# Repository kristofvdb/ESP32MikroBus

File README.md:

# ESP32MikroBus

Minimal ESP32C6 project with Mikrobus and Qwiic header 

I needed a minimal ESP32 project with MikroBus.
Since I couldn't find any, I decided to create it myself.

I also wanted to be able to solder it myself, otherwise I could have made the design more compact.
That is also the reason why there are only components on the top side.

Many thanks to the other folks that also made their design open source, which speeded up this design.

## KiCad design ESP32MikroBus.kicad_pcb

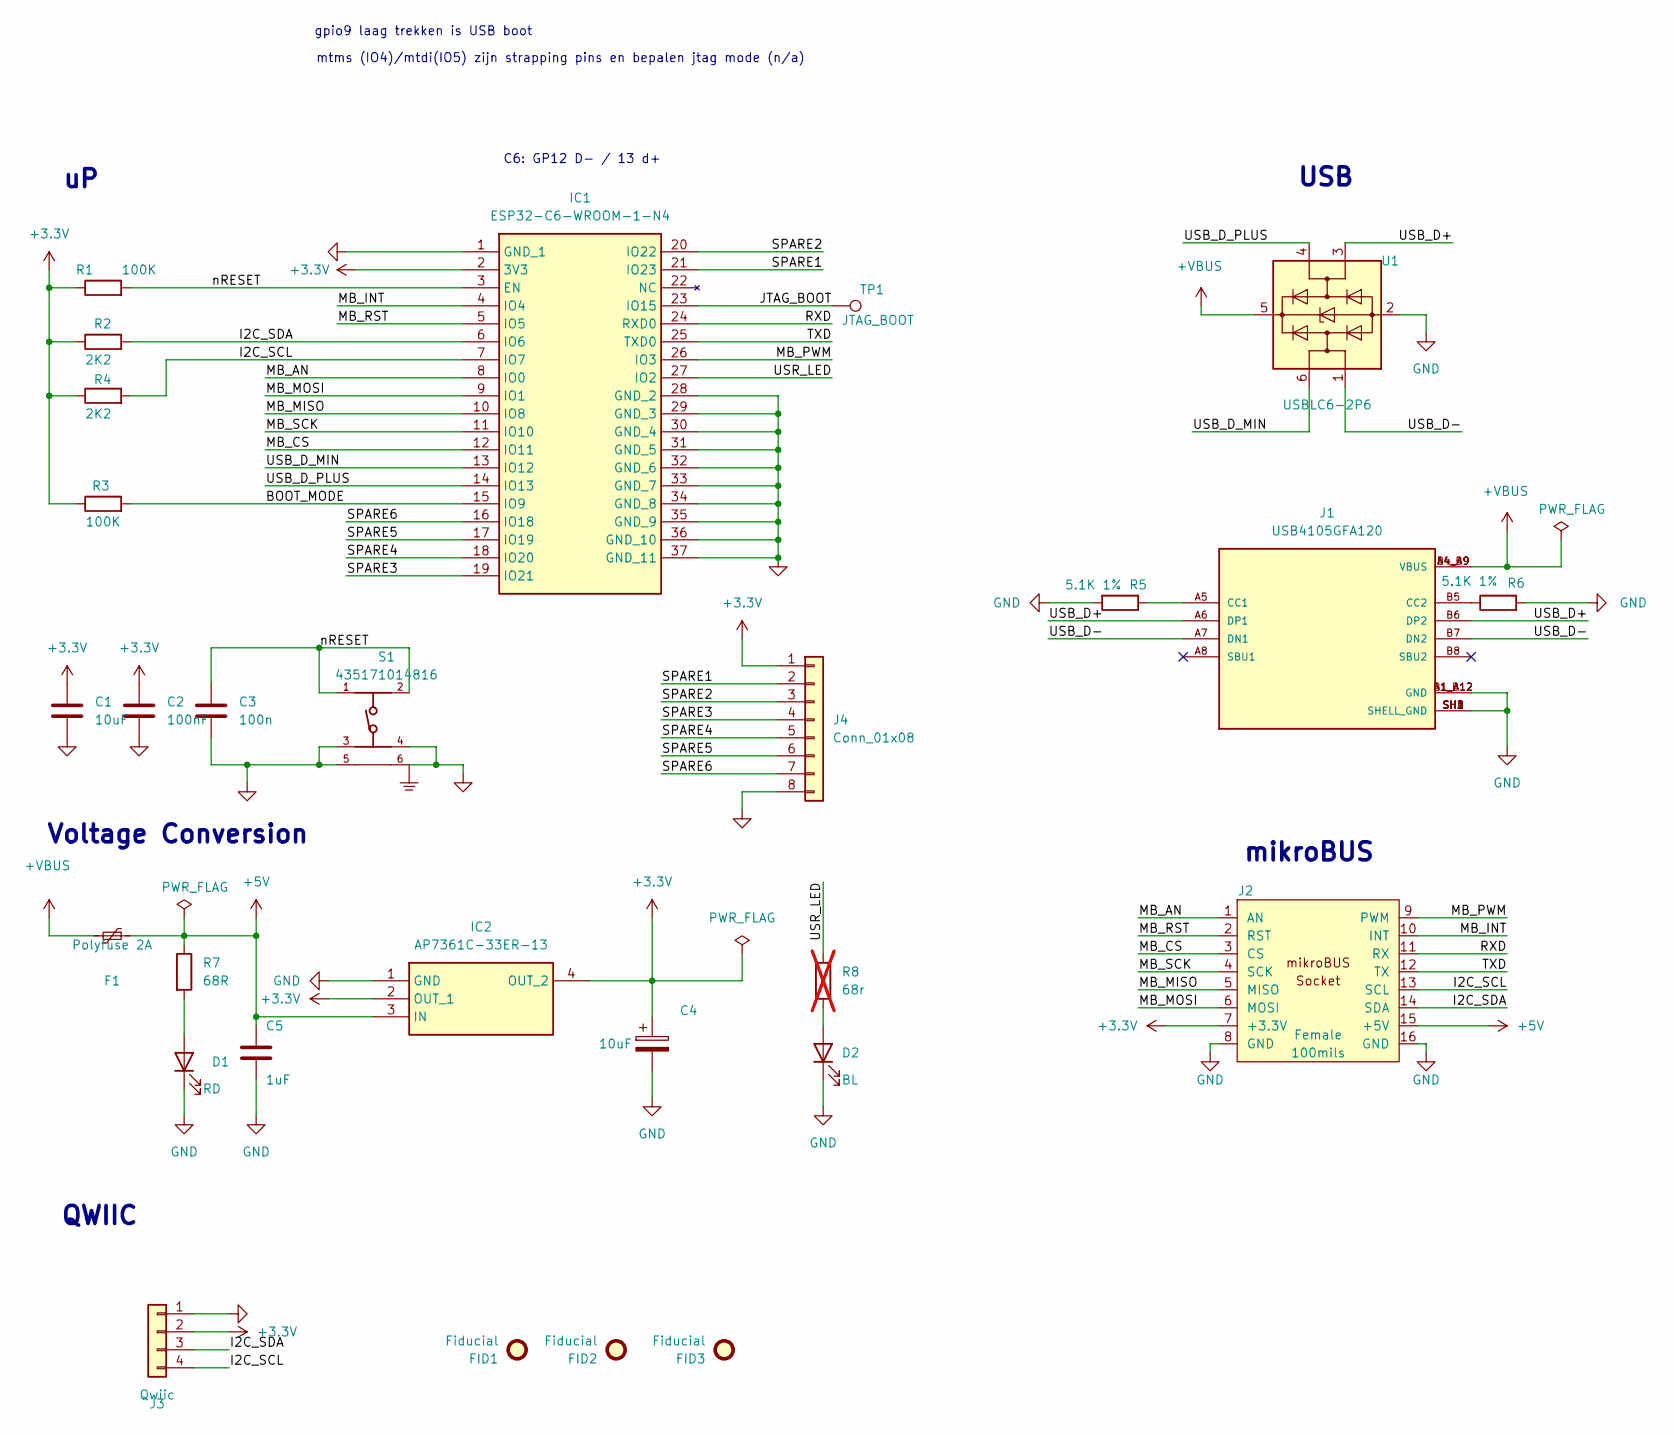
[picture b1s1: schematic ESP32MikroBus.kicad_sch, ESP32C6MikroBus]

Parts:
C1, C4: 10uF; C_0603_1608Metric
C2: 100nF; C_0603_1608Metric
C3: 100n; C_0603_1608Metric
C5: 1uF; C_0603_1608Metric
D1: RD; LED_0805_2012Metric
D2: BL; LED_0805_2012Metric
F1: Polyfuse 2A; FUSC3216X100N
FID1, FID2, FID3: Fiducial; Fiducial_0.5mm_Mask1.5mm
IC1: ESP32-C6-WROOM-1-N4; ESP32C6WROOM1N4; Mouser Part Number 356-ESP32C6WROOM1N4
IC2: AP7361C-33ER-13; SOT230P700X180-4N; Mouser Part Number 621-AP7361C-33ER-13
J1: USB4105GFA120; GCT_USB4105GFA120; PARTREV B3
J2: CON_HDR_MIKROBUS_SOCKET_TH; Voltage 350V
J3: Qwiic; SPARKFUN_PRT-14417
J4: Conn_01x08; PinHeader_1x08_P1.27mm_Vertical
R1, R3: 100K; R_0603_1608Metric
R2, R4: 2K2; R_0603_1608Metric
R5, R6: 5.1K 1%; R_0603_1608Metric
R7: 68R; R_0603_1608Metric
R8: 68r; R_0603_1608Metric; not fitted
S1: 435171014816; PART-NUMBER 435171014816
TP1: JTAG_BOOT; TestPoint_Pad_D1.5mm
U1: USBLC6-2P6; SOT-666

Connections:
+3.3V: C1.1, C2.1, C4.1, IC1.2 (3V3), IC2.2 (OUT_1), IC2.4 (OUT_2), J2.7 (+3.3V), J3.2, J4.1, R1.1, R2.1, R3.1, R4.1
+5V: C5.1, F1.1, IC2.3 (IN), J2.15 (+5V), R7.1
+VBUS: F1.2, J1.A4_B9 (VBUS), J1.B4_A9 (VBUS), U1.5 (VBUS)
/BOOT_MODE: IC1.15 (IO9), R3.2
/I2C_SCL: IC1.7 (IO7), J2.13 (SCL), J3.4, R4.2
/I2C_SDA: IC1.6 (IO6), J2.14 (SDA), J3.3, R2.2
/JTAG_BOOT: IC1.23 (IO15), TP1.1
/MB_AN: IC1.8 (IO0), J2.1 (AN)
/MB_CS: IC1.12 (IO11), J2.3 (CS)
/MB_INT: IC1.4 (IO4), J2.10 (INT)
/MB_MISO: IC1.10 (IO8), J2.5 (MISO)
/MB_MOSI: IC1.9 (IO1), J2.6 (MOSI)
/MB_PWM: IC1.26 (IO3), J2.9 (PWM)
/MB_RST: IC1.5 (IO5), J2.2 (RST)
/MB_SCK: IC1.11 (IO10), J2.4 (SCK)
/RXD: IC1.24 (RXD0), J2.11 (RX)
/SPARE1: IC1.21 (IO23), J4.2
/SPARE2: IC1.20 (IO22), J4.3
/SPARE3: IC1.19 (IO21), J4.4
/SPARE4: IC1.18 (IO20), J4.5
/SPARE5: IC1.17 (IO19), J4.6
/SPARE6: IC1.16 (IO18), J4.7
/TXD: IC1.25 (TXD0), J2.12 (TX)
/USB_D+: J1.A6 (DP1), J1.B6 (DP2), U1.3 (I/O2)
/USB_D-: J1.A7 (DN1), J1.B7 (DN2), U1.1 (I/O1)
/USB_D_MIN: IC1.13 (IO12), U1.6 (I/O1)
/USB_D_PLUS: IC1.14 (IO13), U1.4 (I/O2)
/USR_LED: IC1.27 (IO2), R8.1
/nRESET: C3.1, IC1.3 (EN), R1.2, S1.1, S1.2
GND: C1.2, C2.2, C3.2, C4.2, C5.2, D1.1 (K), D2.1 (K), IC1.1 (GND_1), IC1.28 (GND_2), IC1.29 (GND_3), IC1.30 (GND_4), IC1.31 (GND_5), IC1.32 (GND_6), IC1.33 (GND_7), IC1.34 (GND_8), IC1.35 (GND_9), IC1.36 (GND_10), IC1.37 (GND_11), IC2.1 (GND), J1.A1_B12 (GND), J1.B1_A12 (GND), J1.SH1 (SHELL_GND), J1.SH2 (SHELL_GND), J1.SH3 (SHELL_GND), J1.SH4 (SHELL_GND), J2.8 (GND), J2.16 (GND), J3.1, J4.8, R5.2, R6.2, S1.3, S1.4, S1.5, S1.6, U1.2 (GND)
unnamed: D1.2 (A), R7.2
unnamed: D2.2 (A), R8.2
unnamed: J1.A5 (CC1), R5.1
unnamed: J1.B5 (CC2), R6.1

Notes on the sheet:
mikroBUS
QWIIC
Voltage Conversion
mtms (IO4)/mtdi(IO5) zijn strapping pins en bepalen jtag mode (n/a)
USB
gpio9 laag trekken is USB boot
C6: GP12 D- / 13 d+

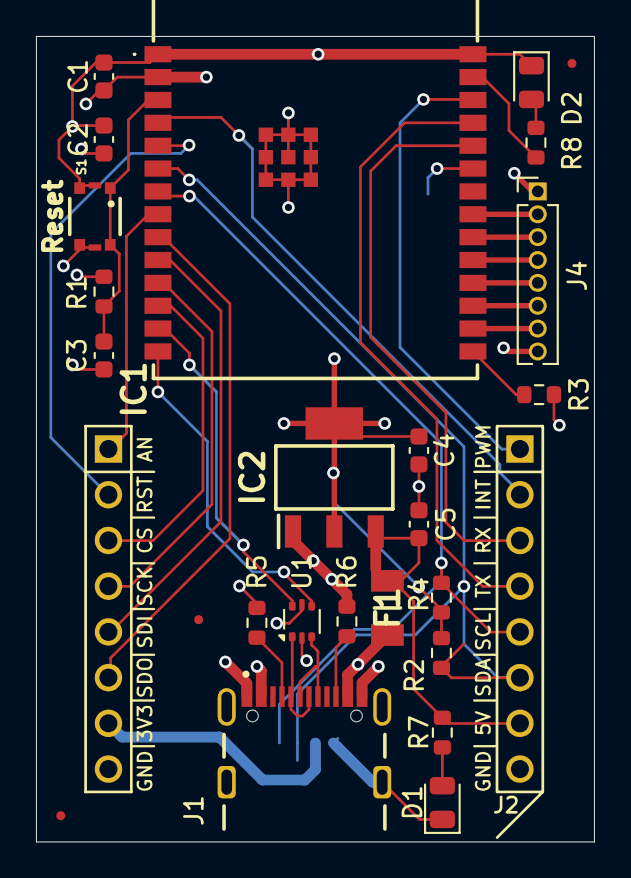
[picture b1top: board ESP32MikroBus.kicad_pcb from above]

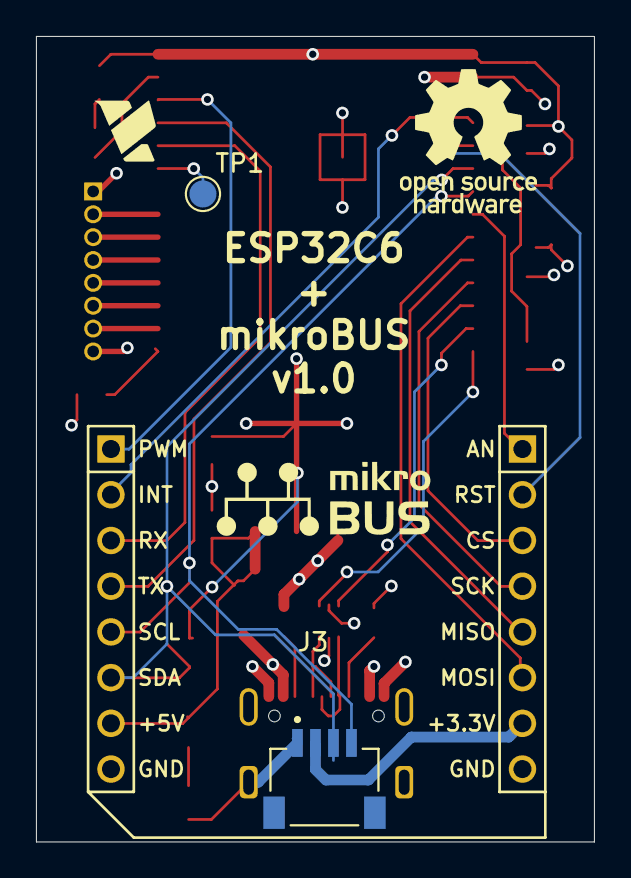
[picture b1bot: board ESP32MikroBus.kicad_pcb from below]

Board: 4 copper layers, 31.0 x 44.8 mm, 28 parts (2 on the bottom side), 34 nets.

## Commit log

2024-12-08 Schematic ready to start PCB design
2024-12-08 PCB Layout v1.0 ready for verification by PCBWay
2024-12-08 Minor update, mainly cosmetical + vbus not connected
2024-12-21 Changed c1 to 10uF, more attention to power traces, fixed copper plane and qwiic connector
